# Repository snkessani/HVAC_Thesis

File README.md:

# HVAC_Thesis
This project presents the PCB design for a compact wireless sensor node tailored for HVAC (Heating, Ventilation, and Air Conditioning) monitoring applications. The board is based on the nRF52832 Bluetooth Low Energy (BLE) 5.0 microcontroller, chosen for its low power consumption, reliable wireless communication, and small footprint. The PCB integrates an environmental sensor (such as a temperature, humidity, or air quality sensor), power management circuitry for battery or regulated power input, and essential components to support BLE connectivity. Designed as part of a larger wireless sensor network, this node transmits real-time environmental data to a central host computer, enabling intelligent monitoring and control of HVAC systems. The design includes a two-layer PCB layout, schematic, and ready-to-use Gerber files, created using KiCad. This hardware serves as a scalable, energy-efficient platform for IoT-based environmental sensing in smart buildings and automation systems.

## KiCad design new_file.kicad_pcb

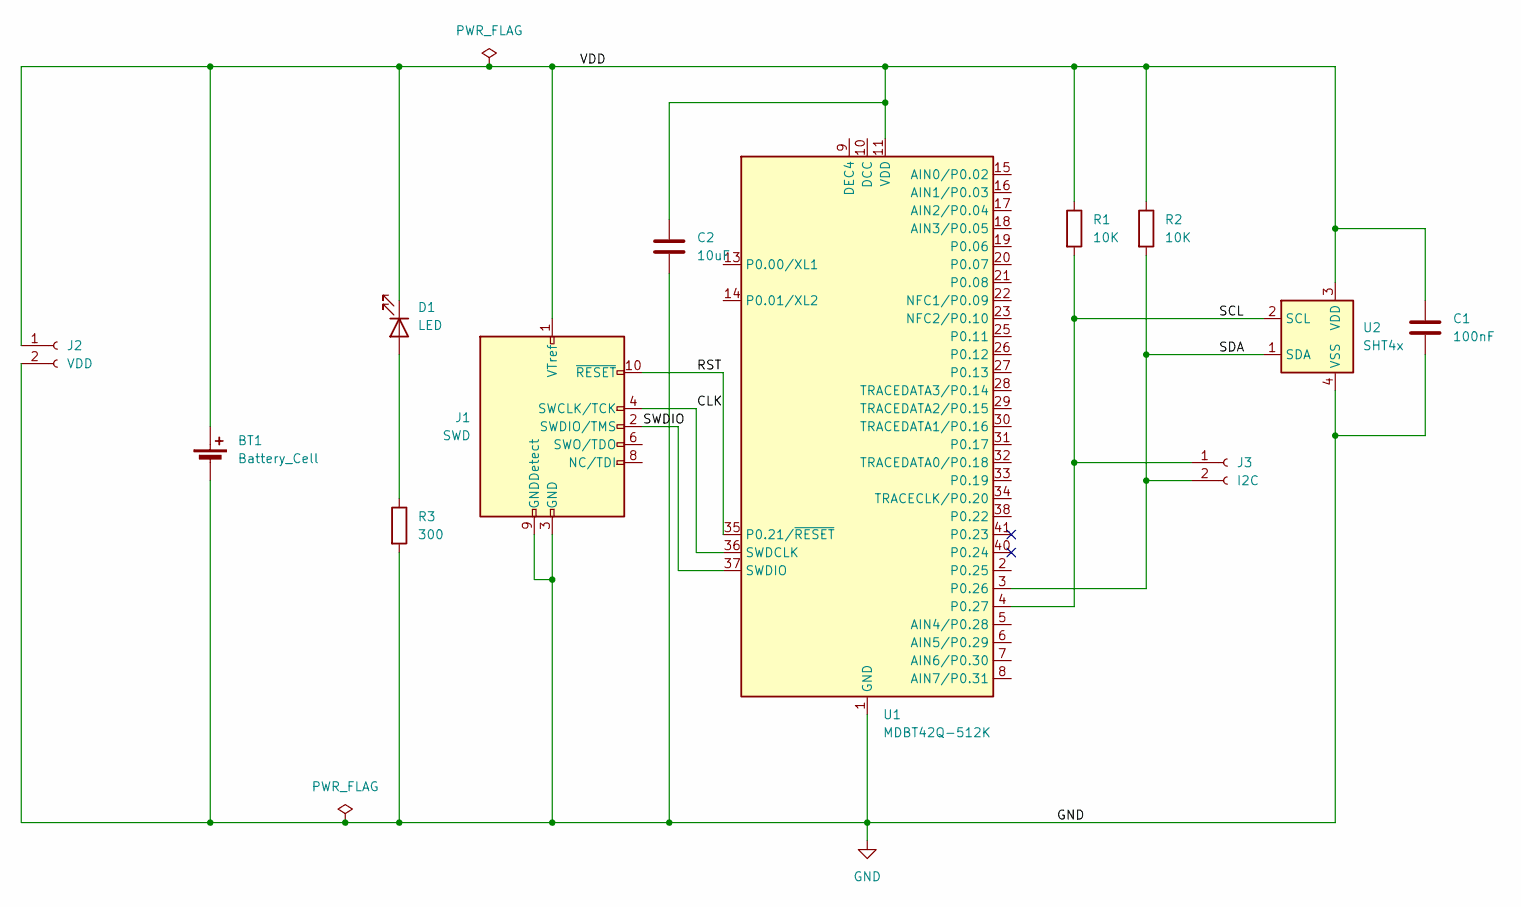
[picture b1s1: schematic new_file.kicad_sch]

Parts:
BT1: Battery_Cell; BH-25C-1_ADM
C1: 100nF; cap_100nf
C2: 10uF; cap_10uf
D1: LED; LED_power
J1: SWD; PinHeader_2x05_P1.27mm_Vertical_SMD
J2: VDD; PinSocket_1x02_P2.54mm_Vertical
J3: I2C; PinSocket_1x02_P2.54mm_Vertical
R1, R2: 10K; res_10k
R3: 300; res_10k
U1: MDBT42Q-512K; Raytac_MDBT42Q
U2: SHT4x; Sensirion_DFN-4_1.5x1.5mm_P0.8mm_SHT4x_NoCentralPad

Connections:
/CLK: J1.4 (SWCLK/TCK), U1.36 (SWDCLK)
/RST: J1.10 (~RESET), U1.35 (P0.21/~RESET)
/SCL: J3.1, R1.2, U1.4 (P0.27), U2.2 (SCL)
/SDA: J3.2, R2.2, U1.3 (P0.26), U2.1 (SDA)
/SWDIO: J1.2 (SWDIO/TMS), U1.37 (SWDIO)
/VDD: BT1.1 (+), C1.1, C2.1, D1.1 (K), J1.1 (VTref), J2.1, R1.1, R2.1, U1.11 (VDD), U2.3 (VDD)
GND: BT1.2 (-), C1.2, C2.2, J1.3 (GND), J1.5 (GND), J1.9 (GNDDetect), J2.2, R3.2, U1.1 (GND), U1.12 (GND), U1.24 (GND), U1.39 (GND), U2.4 (VSS)
unnamed: D1.2 (A), R3.1

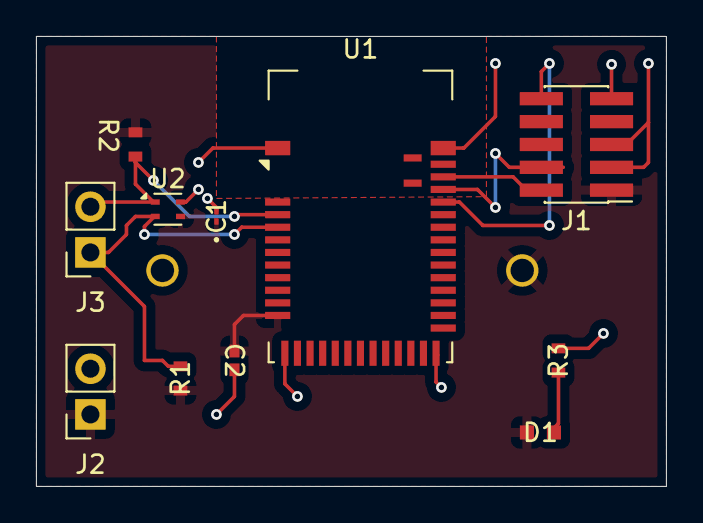
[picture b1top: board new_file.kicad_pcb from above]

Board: 2 copper layers, 35.0 x 25.0 mm, 12 parts (1 on the bottom side), 8 nets.

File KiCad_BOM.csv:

Reference,Qty,Value,DNP,Footprint,Datasheet
BT1,1,Battery_Cell,,bt_holder:BH-25C-1_ADM,~
C1,1,100nF,,bt_holder:cap_100nf (2),~
C2,1,10uF,,bt_holder:cap_10uf,~
D1,1,LED,,bt_holder:LED_power,~
J1,1,SWD,,Connector_PinHeader_1.27mm:PinHeader_2x05_P1.27mm_Vertical_SMD,http://infocenter.arm.com/help/topic/com.arm.doc.ddi0314h/DD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
J2,1,VDD,,Connector_PinSocket_2.54mm:PinSocket_1x02_P2.54mm_Vertical,~
J3,1,I2C,,Connector_PinSocket_2.54mm:PinSocket_1x02_P2.54mm_Vertical,~
"R1,R2",2,10K,,bt_holder:res_10k,~
R3,1,300,,bt_holder:res_10k,~
U1,1,MDBT42Q-512K,,RF_Module:Raytac_MDBT42Q,https://www.raytac.com/download/index.php?index_id=27
U2,1,SHT4x,,Sensor_Humidity:Sensirion_DFN-4_1.5x1.5mm_P0.8mm_SHT4x_NoCentralPad,https://sensirion.com/media/documents/33FD6951/624C4357/Data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
